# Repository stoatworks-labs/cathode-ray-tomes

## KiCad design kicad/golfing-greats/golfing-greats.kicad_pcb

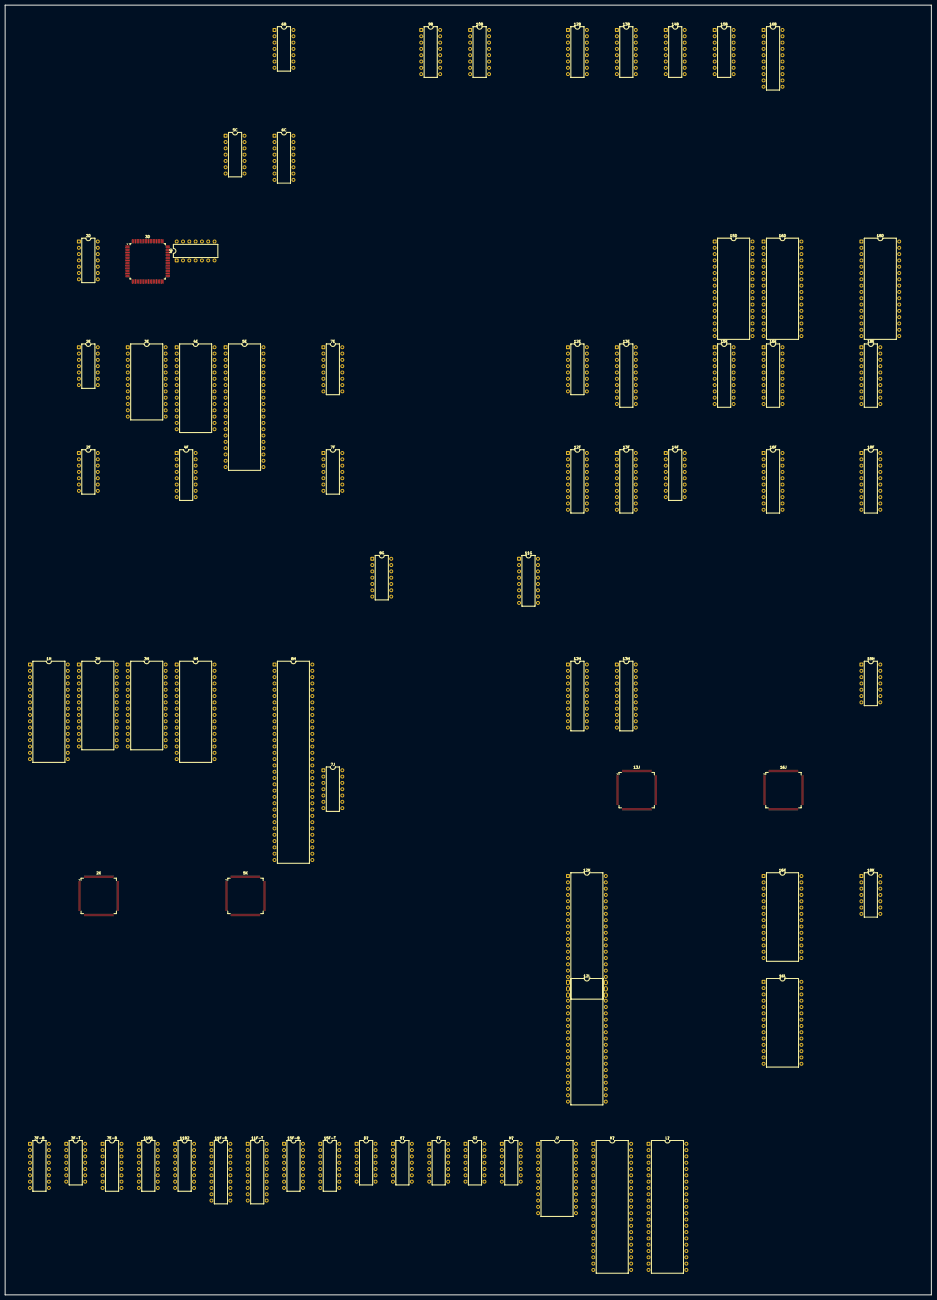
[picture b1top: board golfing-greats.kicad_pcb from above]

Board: 2 copper layers, 373.1 x 519.5 mm, 71 parts (0 on the bottom side), 383 nets, no tracks yet.

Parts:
1H, 4H: 27C010; DIP-32_W15.24mm
2D, 2E, 18K: 74LS74; DIP-14_W7.62mm
2F: 74LS00; DIP-14_W7.62mm
2H, 3H: MB8464A-80-10-15/L-LL; DIP-28_W15.24mm
2K: 053244; TQFP-120_14x14mm_P0.4mm
3D: 053260; PQFP-80_14x14mm_P0.65mm
3E: CY7C128-45PC; DIP-24_W15.24mm
3F-B: 74F139; DIP-16_W7.62mm
3F-T, 7J: 74LS08; DIP-14_W7.62mm
4D: 74LS20; DIP-14_W7.62mm
4E: 27C256; DIP-28_W15.24mm
4F: 74ALS138; DIP-16_W7.62mm
5C, 18H: 74LS32; DIP-14_W7.62mm
5E: Z80CPU; DIP-40_W15.24mm
5K: 053245; TQFP-120_14x14mm_P0.4mm
6B: 74LS04; DIP-14_W7.62mm
6C, 11G: 74LS139; DIP-16_W7.62mm
6H: 68000D; DIP-64_W15.24mm
7E: 74LS367; DIP-16_W7.62mm
7E-B: 74LS138; DIP-16_W7.62mm
7F: 74ALS74; DIP-14_W7.62mm
8G: 74F74; DIP-14_W7.62mm
9B, 10B, 11B1, 11B2, 12B, 13B, 14B, 15B: 74LS253; DIP-16_W7.62mm
11F-B, 13E, 16F, 18F: 74LS374; DIP-20_W7.62mm
11F-T, 13F: 74LS273; DIP-20_W7.62mm
12E: 74LS367_Split2; DIP-16_W7.62mm
12F, 15E, 16E, 18E: 74LS245; DIP-20_W7.62mm
12H, 13H: 007644; DIP-22_W7.62mm
12K, 12L: 955D05-06-07-08; DIP-40_W15.24mm
13J: 051962; TQFP-120_14x14mm_P0.4mm
14F: 74LS157; DIP-16_W7.62mm
15D, 16D, 18D: DIP-32_W15.24mm
15F-B: 74LS153; DIP-16_W7.62mm
15F-T: 74LS175; DIP-16_W7.62mm
16B: DIP-20_W7.62mm
16J: 052109; TQFP-120_14x14mm_P0.4mm
16K, 16L: MB8464A-10W-15W; DIP-28_W15.24mm
D?: 74LS32; DIP-14_W7.62mm
E?: 74LS08; DIP-14_W7.62mm
F?: 74LS157; DIP-14_W7.62mm
G?: 74LS245; DIP-14_W7.62mm
H?: 74LS07; DIP-14_W7.62mm
J?: HM6116P-3; DIP-24_W15.24mm
K?: 065A08; DIP-42_W15.24mm
L?: 065A08; DIP-42_W15.24mm

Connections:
/DB0: 11F-B.2, 12F.2, 12H.10, 13H.3, 15E.2, 16E.2
/DB1: 11F-B.5, 12F.3, 12H.9, 13H.4, 15E.3, 16E.3
/DB2: 11F-B.6, 12F.4, 12H.8, 13H.5, 15E.4, 16E.4
/DB3: 11F-B.9, 12F.5, 12H.7, 13H.6, 15E.5, 16E.5
/DB4: 11F-B.12, 12F.6, 12H.6, 13H.7, 15E.6, 16E.6
/DB5: 11F-B.15, 12F.7, 12H.5, 13H.8, 15E.7, 16E.7
/DB6: 11F-B.16, 12F.8, 12H.4, 13H.9, 15E.8, 16E.8
/DB7: 11F-B.19, 12F.9, 12H.3, 13H.10, 15E.9, 16E.9
/M~RD: 12F.1, 16B.2
/RM~RD: 11F-T.12, 13J.96, 16J.97
/cabinet/AB1: 9B.14, 10B.14, 11B1.14, 11B2.14, 12B.14, 13B.14, 14B.14, 15B.14
/cabinet/AB2: 9B.2, 10B.2, 11B1.2, 11B2.2, 12B.2, 13B.2, 14B.2, 15B.2
/cabinet/DB0: 10B.7, 11F-T.3
/cabinet/DB1: 10B.9, 11F-T.4
/cabinet/DB2: 11F-T.7, 14B.7
/cabinet/DB3: 11F-T.8, 14B.9
/cabinet/DB4: 11F-T.13, 15B.7
/cabinet/DB5: 11F-T.14, 15B.9
/cabinet/DB6: 11B1.7, 11F-T.17
/cabinet/DB7: 11B1.9, 11F-T.18
/cabinet/DB8: 12B.7, 16B.18
/cabinet/DB9: 12B.9, 16B.17
/cabinet/DB10: 11B2.7, 16B.16
/cabinet/DB12: 13B.7, 16B.14
/cabinet/DB13: 13B.9, 16B.15
/cabinet/DB14: 9B.7, 16B.12
/cabinet/DB15: 9B.9, 16B.11
/cabinet/VSS: 16B.8, 16B.10
/cabinet/~INTR: 11B1.10, 16B.5
/main/052109: 3F-B.1, 3F-B.10
/main/$30: 2F.10, 3F-B.9, 11G.1
/main/A1: 1H.12, 2H.10, 3H.10, 4H.12, 6H.29, 12E.2
/main/A2: 1H.11, 2H.9, 3H.9, 4H.11, 6H.30, 12E.4
/main/A3: 1H.10, 2H.8, 3H.8, 4H.10, 6H.31, 12E.6
/main/A4: 1H.9, 2H.7, 3H.7, 4H.9, 6H.32, 12E.10
/main/A5: 1H.8, 2H.6, 3H.6, 4H.8, 6H.33
/main/A6: 1H.7, 2H.5, 3H.5, 4H.7, 6H.34
/main/A7: 1H.6, 2H.4, 3H.4, 4H.6, 6H.35
/main/A8: 1H.5, 2H.3, 3H.3, 4H.5, 6H.36
/main/A9: 1H.27, 2H.25, 3H.25, 4H.27, 6H.37
/main/A10: 1H.26, 2H.24, 3H.24, 4H.26, 6H.38
/main/A11: 1H.23, 2H.21, 3H.21, 4H.23, 6H.39
/main/A12: 1H.25, 2H.23, 3H.23, 4H.25, 6H.40, 7E-B.1
/main/A13: 1H.4, 2H.2, 3H.2, 4H.4, 6H.41, 7E-B.2
/main/A14: 1H.28, 4F.1, 4H.28, 6H.42, 7E-B.3
/main/A15: 1H.29, 4F.2, 4H.29, 6H.43
/main/A16: 1H.3, 4F.3, 4H.3, 6H.44
/main/A17: 1H.2, 4F.5, 4H.2, 6H.45, 7E-B.6
/main/A19: 6H.47, 11G.2
/main/A20: 3F-B.14, 6H.48
/main/A21: 3F-B.13, 6H.50
/main/A23: 2F.5, 6H.52
/main/D0: 3H.11, 4H.13, 6H.5, 12H.13
/main/D1: 3H.12, 4H.14, 6H.4, 12H.14
/main/D2: 3H.13, 4H.15, 6H.3, 12H.15
/main/D3: 3H.15, 4H.17, 6H.2, 12H.16
/main/D4: 3H.16, 4H.18, 6H.1, 12H.17
/main/D5: 3H.17, 4H.19, 6H.64, 12H.18
/main/D6: 3H.18, 4H.20, 6H.63, 12H.19
/main/D7: 3H.19, 4H.21, 6H.62, 12H.20
/main/D8: 1H.13, 2H.11, 6H.61, 13H.13
/main/D9: 1H.14, 2H.12, 6H.60, 13H.14
/main/D10: 1H.15, 2H.13, 6H.59, 13H.15
/main/D11: 1H.17, 2H.15, 6H.58, 13H.16
/main/D12: 1H.18, 2H.16, 6H.57, 13H.17
/main/D13: 1H.19, 2H.17, 6H.56, 13H.18
/main/D14: 1H.20, 2H.18, 6H.55, 13H.19
/main/D15: 1H.21, 2H.19, 6H.54, 13H.20
/main/PAS: 2E.10, 2F.4, 4D.13, 4F.6, 6B.2
/main/R/~W: 3F-B.3, 6H.9
/main/~AS: 6B.1, 6H.6, 7E-B.5, 7F.12
/main/~CFG: 2E.3, 7E-B.13
/main/~ROM: 1H.24, 3F-B.12, 4H.24
/main/~UDS: 3F-B.2, 6H.7
/objects/AR0: 2K.30, 5K.119
/objects/AR1: 2K.32, 5K.118
/objects/AR2: 2K.33, 5K.117
/objects/AROK: 2K.34, 5K.116
/objects/BK0: J?.9, K?.36, L?.36
/objects/BK1: J?.10, K?.35, L?.35
/objects/BK2: J?.11, K?.34, L?.34
/objects/BK3: J?.13, K?.33, L?.33
/objects/BK4: J?.14, L?.2
/objects/BK5: J?.15, K?.13, L?.1
/objects/BR0: 2K.35, 5K.115
/objects/BR1: 2K.36, 5K.114
/objects/BR2: 2K.37, 5K.113
/objects/BROK: 2K.38, 5K.112
/objects/CLAT: 2K.64, 5K.86
/objects/HP0: 2K.54, 5K.96
/objects/HP1: 2K.53, 5K.97
/objects/HP2: 2K.52, 5K.98
/objects/HP3: 2K.50, 5K.99
/objects/HP4: 2K.49, 5K.100
/objects/HP5: 2K.48, 5K.102
/objects/HP6: 2K.47, 5K.103
/objects/HP7: 2K.45, 5K.104
/objects/HP8: 2K.44, 5K.105
/objects/HP9: 2K.43, 5K.107
/objects/HRFP: 2K.39, 5K.110
/objects/M6: 2K.10, 5K.10
/objects/M12: 2K.12, 5K.12
/objects/MAIN_A2: 2K.18, 5K.25
/objects/MAIN_A3: 2K.17, 5K.24
/objects/MAIN_A4: 2K.15, 5K.23
/objects/M~RD: 2K.20, 5K.13, F?.11
/objects/OBJROMA0: 5K.85, L?.10
/objects/OBJROMA1: 5K.84, K?.9, L?.9
/objects/OBJROMA2: 5K.83, L?.8
/objects/OBJROMA3: 5K.82, K?.7, L?.7
/objects/OBJROMA4: 5K.80, K?.6, L?.6
/objects/OBJROMA5: 5K.79, K?.5, L?.5
/objects/OBJROMA6: 5K.78, K?.4, L?.4
/objects/OBJROMA7: 5K.77, K?.3, L?.3
/objects/OBJROMA8: 5K.75, K?.41, L?.41
/objects/OBJROMA9: 5K.74, K?.40, L?.40
/objects/OBJROMA10: 5K.73, K?.39, L?.39
/objects/OBJROMA11: 5K.72, K?.38, L?.38
/objects/OBJROMA12: 5K.70, K?.37, L?.37
/objects/OBJROMA13: 5K.69, K?.2
/objects/OBJROMA14: 5K.68, G?.6
/objects/OBJROMA16: 5K.66, K?.10
/objects/OBJROMA17: 5K.65, F?.3
/objects/OBJROMA18: 5K.64, F?.6
/objects/OBJROMD2: 2K.98, K?.18, L?.18
/objects/OBJROMD3: 2K.97, K?.20, L?.20
/objects/OBJROMD4: 2K.96, K?.23, L?.23
/objects/OBJROMD5: 2K.95, K?.25, L?.25
/objects/OBJROMD6: 2K.94, K?.27, L?.27
/objects/OBJROMD7: 2K.93, K?.29, L?.29
/objects/OBJROMD8: 2K.92, L?.15
/objects/OBJROMD9: 2K.90, K?.17, L?.17
/objects/OBJROMD16: 2K.83, K?.14, L?.14
/objects/OBJROMD17: 2K.82, L?.16
/objects/OBJROMD26: 2K.70, K?.19, L?.19
/objects/OBJROMD27: 2K.69, K?.21, L?.21
/objects/OBJROMD28: 2K.68, K?.24, L?.24
/objects/OBJROMD29: 2K.67, K?.26, L?.26
/objects/OBJROMD30: 2K.66, K?.28, L?.28
/objects/OBJROMD31: 2K.65, K?.30, L?.30
/objects/PL0: 2K.63, 5K.87
/objects/PL1: 2K.62, 5K.88
/objects/PL2: 2K.60, 5K.89
/objects/PL3: 2K.59, 5K.90
/objects/PL4: 2K.58, 5K.92
/objects/PL5: 2K.57, 5K.93
/objects/PL6: 2K.56, 5K.94
/objects/RA1: 5K.52, G?.9
/objects/RA3: 5K.54, G?.7
/objects/RA5: G?.5, G?.8
/objects/RA6: 5K.55, G?.4
/objects/RA7: 5K.56, G?.3
/objects/RA12: 5K.63, G?.2
/objects/RD2: 5K.43, G?.13
/objects/RD14: 5K.28, G?.12
/objects/RD15: 5K.27, G?.11
/objects/SHADOW: 2K.55, 5K.95
/objects/~HIT: 2K.42, 5K.108
/objects/~HSYNC: 2K.8, 5K.4
/objects/~LDS: 5K.9, E?.2
/objects/~OVRC: F?.1, G?.1
/objects/~RESET: 2K.3, 5K.3
/objects/~UDS: 2K.19, 5K.8, E?.1
/objects/~VSYNC: 2K.9, 5K.5
/objects/~ZLD: 2K.40, 5K.109
/scroll/COL5: 13J.109, 16J.42
/scroll/COL6: 13J.108, 16J.43
/scroll/COL7: 13J.107, 16J.46
/scroll/GFXROMA0: 12K.9, 12L.9, 16J.35
/scroll/GFXROMA1: 12K.8, 12L.8, 16J.34
/scroll/GFXROMA2: 12K.7, 12L.7, 16J.33
/scroll/GFXROMA3: 12K.6, 12L.6, 16J.32
/scroll/GFXROMA4: 12K.5, 12L.5, 16J.30
/scroll/GFXROMA5: 12K.4, 12L.4, 16J.29
/scroll/GFXROMA6: 12K.3, 12L.3, 16J.28
/scroll/GFXROMA7: 12K.2, 12L.2, 16J.27
/scroll/GFXROMA8: 12K.40, 12L.40, 16J.26
/scroll/GFXROMA9: 12K.39, 12L.39, 16J.25
/scroll/GFXROMA10: 12K.38, 12L.38, 16J.24
/scroll/GFXROMA11: 12K.37, 12L.37, 16J.37
/scroll/GFXROMA12: 12K.36, 12L.36, 16J.38
/scroll/GFXROMA13: 12K.35, 12L.35, 16J.41
/scroll/GFXROMA14: 12K.34, 12L.34, 16J.39
/scroll/GFXROMA15: 12K.33, 12L.33, 16J.40
/scroll/GFXROMA16: 12K.32, 12L.32, 16J.23
/scroll/GFXROMA17: 12K.1, 12L.1, 16J.22
/scroll/GFXROMD0: 12L.13, 13J.29
/scroll/GFXROMD1: 12L.15, 13J.28
/scroll/GFXROMD2: 12L.17, 13J.27
/scroll/GFXROMD3: 12L.19, 13J.26
/scroll/GFXROMD4: 12L.22, 13J.25
/scroll/GFXROMD5: 12L.24, 13J.24
/scroll/GFXROMD6: 12L.26, 13J.23
/scroll/GFXROMD7: 12L.28, 13J.22
/scroll/GFXROMD8: 12L.14, 13J.21
/scroll/GFXROMD9: 12L.16, 13J.20
/scroll/GFXROMD10: 12L.18, 13J.19
/scroll/GFXROMD11: 12L.20, 13J.18
/scroll/GFXROMD12: 12L.23, 13J.17
/scroll/GFXROMD13: 12L.25, 13J.16
/scroll/GFXROMD14: 12L.27, 13J.13
/scroll/GFXROMD15: 12L.29, 13J.12
/scroll/GFXROMD16: 12K.13, 13J.11
/scroll/GFXROMD17: 12K.15, 13J.10
/scroll/GFXROMD18: 12K.17, 13J.9
/scroll/GFXROMD19: 12K.19, 13J.8
/scroll/GFXROMD20: 12K.22, 13J.7
/scroll/GFXROMD21: 12K.24, 13J.6
/scroll/GFXROMD22: 12K.26, 13J.5
/scroll/GFXROMD23: 12K.28, 13J.4
/scroll/GFXROMD24: 12K.14, 13J.3
/scroll/GFXROMD25: 12K.16, 13J.2
/scroll/GFXROMD26: 12K.18, 13J.120
/scroll/GFXROMD27: 12K.20, 13J.119
/scroll/GFXROMD28: 12K.23, 13J.118
/scroll/GFXROMD29: 12K.25, 13J.117
/scroll/GFXROMD30: 12K.27, 13J.116
/scroll/GFXROMD31: 12K.29, 13J.115
/scroll/MAIN_A1: 13J.88, 16J.66
/scroll/MAIN_A2: 13J.89, 16J.67
/scroll/MAIN_DB0: 13J.79, 16J.56
/scroll/MAIN_DB1: 13J.80, 16J.57
/scroll/MAIN_DB2: 13J.81, 16J.58
/scroll/MAIN_DB3: 13J.82, 16J.59
/scroll/MAIN_DB4: 13J.83, 16J.60
/scroll/MAIN_DB5: 13J.84, 16J.62
/scroll/MAIN_DB7: 13J.86, 16J.64
/scroll/M~RD: 13J.87, 16J.85
/scroll/SCRAMA0: 16J.2, 16K.10, 16L.10
/scroll/SCRAMA1: 16J.120, 16K.9, 16L.9
/scroll/SCRAMA2: 16J.119, 16K.8, 16L.8
/scroll/SCRAMA3: 16J.118, 16K.7, 16L.7
/scroll/SCRAMA4: 16J.117, 16K.6, 16L.6
/scroll/SCRAMA5: 16J.70, 16K.5, 16L.5
/scroll/SCRAMA6: 16J.71, 16K.4, 16L.4
/scroll/SCRAMA7: 16J.72, 16K.3, 16L.3
/scroll/SCRAMA8: 16J.73, 16K.25, 16L.25
/scroll/SCRAMA9: 16J.76, 16K.24, 16L.24
/scroll/SCRAMA10: 16J.77, 16K.21, 16L.21
/scroll/SCRAMA11: 16J.78, 16K.23, 16L.23
/scroll/SCRAMA12: 16J.79, 16K.2, 16L.2
/scroll/SCR~CLK: 13J.90, 16J.65
/scroll/VD0: 16J.20, 16K.11
/scroll/VD1: 16J.19, 16K.12
/scroll/VD2: 16J.18, 16K.13
/scroll/VD3: 16J.17, 16K.15
/scroll/VD4: 16J.16, 16K.16
/scroll/VD5: 16J.13, 16K.17
/scroll/VD6: 16J.12, 16K.18
/scroll/VD7: 16J.11, 16K.19
/scroll/VD8: 16J.10, 16L.11
/scroll/VD9: 16J.9, 16L.12
/scroll/VD10: 16J.8, 16L.13
/scroll/VD11: 16J.7, 16L.15
/scroll/VD12: 16J.6, 16L.16
/scroll/VD13: 16J.5, 16L.17
/scroll/VD14: 16J.4, 16L.18
/scroll/VD15: 16J.3, 16L.19
/scroll/ZA1H: 13J.101, 16J.50
/scroll/ZA2H: 13J.100, 16J.51
/scroll/ZA4H: 13J.99, 16J.52
/scroll/ZB1H: 13J.106, 16J.47
/scroll/ZB2H: 13J.103, 16J.48
/scroll/ZB4H: 13J.102, 16J.49
/scroll/~BE: 13J.98, 16J.53
/scroll/~RCS1: 16J.93, 16L.20
/scroll/~RESET: 13J.92, 16J.55
/scroll/~ROE1: 16J.95, 16L.22
/scroll/~ROE2: 16J.96, 16K.22
/scroll/~RWE1: 16J.107, 16L.27
/scroll/~RWE2: 16J.108, 16K.27
/scroll/~VRAM: 13J.97, 16J.54, 16J.84
/sound/A0: 3E.8, 5E.30
/sound/A1: 3E.7, 5E.31
/sound/A2: 3E.6, 5E.32
/sound/A3: 3E.5, 5E.33
/sound/A4: 3E.4, 5E.34
/sound/A5: 3E.3, 5E.35
/sound/A6: 3E.2, 5E.36
/sound/A7: 3E.1, 5E.37
/sound/A8: 3E.23, 5E.38
/sound/A9: 3E.22, 5E.39, 6C.2
/sound/A10: 3E.19, 5E.40, 6C.3
/sound/A11: 5E.1, 6C.14
/sound/A12: 4D.5, 5E.2
/sound/A13: 4D.4, 5E.3
/sound/A14: 4D.2, 5E.4
/sound/A15: 4D.1, 5E.5
/sound/D0: 3E.9, 4E.11, 5E.14
/sound/D1: 3E.10, 4E.12, 5E.15
/sound/D2: 3E.11, 4E.13, 5E.12
/sound/D3: 3E.13, 4E.15, 5E.8
/sound/D4: 3E.14, 4E.16, 5E.7
/sound/D5: 3E.15, 4E.17, 5E.9
/sound/D6: 3E.16, 4E.18, 5E.10
/sound/D7: 3E.17, 4E.19, 5E.13
/sound/SH1: 2D.3, 3D.26
/sound/TIM2: 2D.11, 3D.64
/sound/~IORQ: 5E.20, 7J.12
/sound/~MREQ: 5C.4, 5E.19
/sound/~NMICLR: 2D.4, 6C.5
/sound/~PCMCS: 3D.72, 6C.4
/sound/~RAM: 3E.18, 6C.10
/sound/~RD: 3E.20, 4E.22, 5E.21
/sound/~RFSH: 5E.28, 6C.13
/sound/~RST: 2D.1, 5E.26, 7J.13
/sound/~WR: 3E.21, 5E.22
/zlayer/D0: 15D.13, 15E.18, 15F-B.6
/zlayer/D1: 15D.14, 15E.17, 15F-B.10
/zlayer/D2: 15D.15, 15E.16, 15F-B.5
/zlayer/D3: 15D.17, 15E.15, 15F-B.11
/zlayer/D4: 15D.18, 15E.14, 15F-B.4
/zlayer/D5: 15D.19, 15E.13, 15F-B.12
/zlayer/D6: 15D.20, 15E.12, 15F-B.3
/zlayer/D7: 15D.21, 15E.11, 15F-B.13
/zlayer/D8: 16D.13, 16E.18
/zlayer/D9: 16D.14, 16E.17
/zlayer/D10: 16D.15, 16E.16
/zlayer/D11: 16D.17, 16E.15
/zlayer/D12: 16D.18, 16E.14
/zlayer/D13: 16D.19, 16E.13
/zlayer/D14: 16D.20, 16E.12
/zlayer/D15: 16D.21, 16E.11
/zlayer/D16: 18D.13, 18E.18, 18F.3
/zlayer/D17: 18D.14, 18E.17, 18F.4
/zlayer/D18: 18D.15, 18E.16, 18F.7
/zlayer/D19: 18D.17, 18E.15, 18F.8
/zlayer/D20: 18D.18, 18E.14, 18F.13
/zlayer/D21: 18D.19, 18E.13, 18F.14
/zlayer/D22: 18D.20, 18E.12, 18F.17
/zlayer/D23: 18D.21, 18E.11, 18F.18
/zlayer/J0: 12F.18, 14F.2
/zlayer/J1: 12F.17, 14F.5
/zlayer/J2: 12F.16, 14F.11
/zlayer/J3: 12F.15, 14F.14
/zlayer/J4: 12F.14, 14F.3
/zlayer/J5: 12F.13, 14F.6
/zlayer/J6: 12F.12, 14F.10
/zlayer/J7: 12F.11, 14F.13
/zlayer/X0: 11F-B.3, 13F.2
/zlayer/X1: 11F-B.4, 13F.6
/zlayer/X2: 11F-B.7, 13F.12
/zlayer/X3: 11F-B.8, 13F.16
/zlayer/X4: 11F-B.13, 13F.5
/zlayer/X5: 11F-B.14, 13F.9
/zlayer/X6: 11F-B.17, 13F.15
/zlayer/X7: 11F-B.18, 13F.19
/zlayer/Y0: 13F.3, 14F.4
/zlayer/Y2: 13F.7, 14F.7
/zlayer/Y4: 13F.13, 14F.9
/zlayer/Y6: 13F.17, 14F.12
/~ADC: 2F.9, 7E-B.12, 16B.1
/~IO: 7E-B.15, 9B.1, 9B.15, 10B.1, 10B.15, 11B1.1, 11B1.15, 11B2.1, 11B2.15, 12B.1, 12B.15, 13B.1, 13B.15, 14B.1, 14B.15, 15B.1, 15B.15
/~RCK: 7E-B.14, 11F-B.1
/~SCRIRQ: 6H.23, 6H.25, 16J.87
/~ZXRMRD: 3F-T.6, 7E.1, 7E.15, 12F.19
GND: 4F.8, 7E.8, 7E-B.8, 9B.8, 10B.8, 11B1.8, 11B2.8, 11F-T.10, 12B.8, 13B.8, 13F.10, 14B.8, 15B.8, 15F-T.8
unnamed: 2D.5, 5E.17
unnamed: 2D.8, 5E.16
unnamed: 2D.13, 7J.11
unnamed: 3F-B.11, 4F.4, 7E-B.4
unnamed: 4D.6, 5C.5
unnamed: 4D.8, 7J.2
unnamed: 6C.1, 6C.9
unnamed: 5C.6, 6C.15
unnamed: 6H.15, 8G.5
unnamed: 6H.10, 7J.3
unnamed: 2F.6, 6H.21
unnamed: 8G.2, 8G.6
unnamed: 3F-T.5, 11G.6
unnamed: 3F-T.4, 11G.7
unnamed: 12E.3, 12E.12
unnamed: 12E.5, 12E.14
unnamed: 12H.21, 13H.21, 18H.3
unnamed: 3F-B.5, 12H.2
unnamed: 13E.2, 14F.1
unnamed: 3F-B.4, 13H.2
unnamed: 15F-B.7, 15F-T.5
unnamed: 15F-B.9, 15F-T.13
unnamed: 7F.10, 18H.1
unnamed: 18H.2, 18K.12
VCC: 2D.10, 2D.12, 2H.28, 2K.16, 2K.46, 2K.76, 2K.106, 3E.24, 3H.28, 4E.28, 4F.16, 5E.11, 5K.16, 5K.46, 5K.60, 5K.76, 5K.106, 5K.120, 6H.12, 6H.13, 6H.22, 6H.24, 7E.16, 7E-B.16, 9B.10, 9B.11, 9B.16, 10B.16, 11B1.11, 11B1.16, 11B2.16, 11F-T.20, 12B.16, 12H.1, 12H.22, 12K.21, 12K.31, 12L.21, 12L.31, 13B.16, 13F.1, 13F.20, 13H.1, 13H.22, 13J.14, 13J.44, 13J.74, 13J.104, 14B.16, 15B.16, 15F-T.16, 16B.20, 16J.14, 16J.44, 16J.74, 16J.104, 16K.26, 16K.28, 16L.26, 16L.28, J?.24, K?.16, K?.22, K?.31, K?.32, L?.22, L?.31, L?.32, L?.42
VSS: 1H.22, 2D.2, 2H.14, 2H.20, 2K.1, 2K.2, 2K.4, 2K.5, 2K.6, 2K.7, 2K.11, 2K.21, 2K.31, 2K.41, 2K.51, 2K.61, 2K.71, 2K.81, 2K.91, 2K.101, 2K.111, 3E.12, 3F-B.15, 3H.14, 3H.20, 4E.14, 4H.22, 5E.29, 5K.1, 5K.2, 5K.11, 5K.21, 5K.31, 5K.41, 5K.51, 5K.61, 5K.71, 5K.81, 5K.91, 5K.101, 5K.111, 12E.1, 12E.15, 12H.11, 12K.10, 12K.11, 12K.12, 12K.30, 12L.10, 12L.11, 12L.12, 12L.30, 13H.11, 13J.1, 13J.15, 13J.31, 13J.45, 13J.61, 13J.75, 13J.91, 13J.94, 13J.105, 13J.110, 13J.111, 13J.112, 13J.113, 13J.114, 16J.1, 16J.15, 16J.21, 16J.31, 16J.36, 16J.45, 16J.61, 16J.75, 16J.91, 16J.105, 16K.14, 16K.20, 16L.14, F?.9, F?.10, G?.14, J?.12, J?.18, J?.19, J?.22, K?.1, K?.8, K?.11, K?.12, K?.15, L?.11, L?.12, L?.13
